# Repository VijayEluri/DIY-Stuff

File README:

Random DIY stuff 
- PCB designs
- CNC projects and motor stepper drivers
- for Arduino Duemilanove
- Python (pygame)

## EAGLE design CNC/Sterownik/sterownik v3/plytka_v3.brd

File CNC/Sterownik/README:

Copyrights - Soki from Elektroda forum - www.elektroda.pl/rtvforum/profile.php?mode=viewprofile&u=8826

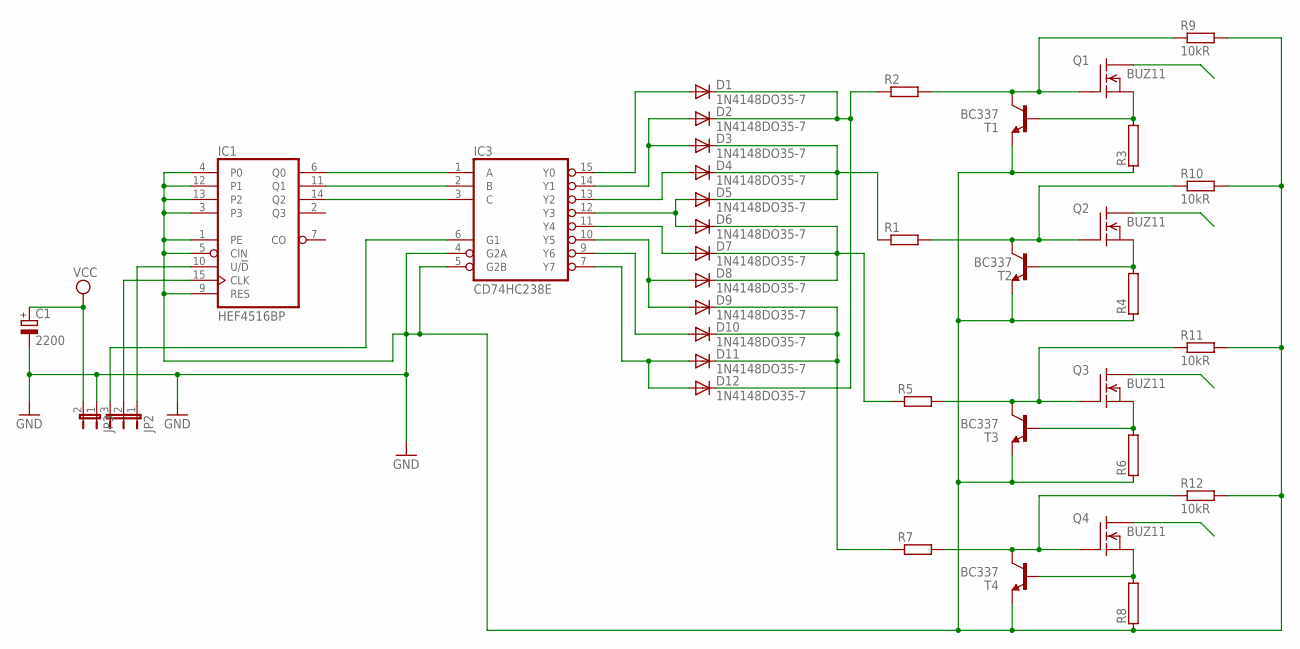
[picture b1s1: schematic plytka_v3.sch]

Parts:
C1: 2200; E5-10,5
D1, D2, D3, D4, D5, D6, D7, D8, D9, D10, D11, D12: 1N4148DO35-7; DO35-7
IC1: HEF4516BP; DIL16
IC3: CD74HC238E; DIL16
JP2: JP2E; JP2
JP3: JP1E; JP1
Q1, Q2, Q3, Q4: BUZ11; TO220
R1, R2, R5, R7: R-EU_0207/15; 0207/15
R3, R4, R6, R8: RKH208-8R; KH208R-8
R9, R10, R11, R12: 10kR; 0207/7
T1, T2, T3, T4: BC337; TO92

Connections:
GND: C1.-, IC1.1 (PE), IC1.3, IC1.4 (P0), IC1.5 (CIN), IC1.8 (VSS), IC1.9 (RES), IC1.12 (P1), IC1.13 (P2), IC3.4 (G2A), IC3.5 (G2B), IC3.8 (GND), JP3.1, R3.1, R4.1, R6.1, R8.1, R9.2, R10.2, R11.2, R12.2, T1.1 (E), T2.1 (E), T3.1 (E), T4.1 (E)
unnamed: IC1.14 (Q2), IC3.3 (C)
unnamed: IC1.11 (Q1), IC3.2 (B)
unnamed: IC1.6 (Q0), IC3.1 (A)
unnamed: IC1.15 (CLK), JP2.2
unnamed: IC1.10 (U/!D), JP2.1
unnamed: IC3.6 (G1), JP2.3
unnamed: D1.A, IC3.15 (Y0)
unnamed: D2.A, D3.A, IC3.14 (Y1)
unnamed: D4.A, IC3.13 (Y2)
unnamed: D5.A, D6.A, IC3.12 (Y3)
unnamed: D7.A, IC3.11 (Y4)
unnamed: D8.A, D9.A, IC3.10 (Y5)
unnamed: D10.A, IC3.9 (Y6)
unnamed: D11.A, D12.A, IC3.7 (Y7)
unnamed: D3.C, D4.C, D5.C, R1.1
unnamed: D9.C, D10.C, D11.C, R7.1
unnamed: Q1.1 (G), R2.2, R9.1, T1.3 (C)
unnamed: Q2.1 (G), R1.2, R10.1, T2.3 (C)
unnamed: Q1.3 (S), R3.2, T1.2 (B)
unnamed: Q2.3 (S), R4.2, T2.2 (B)
unnamed: D6.C, D7.C, D8.C, R5.1
unnamed: Q4.1 (G), R7.2, R12.1, T4.3 (C)
unnamed: Q3.1 (G), R5.2, R11.1, T3.3 (C)
unnamed: Q4.3 (S), R8.2, T4.2 (B)
unnamed: D1.C, D2.C, D12.C, R2.1
unnamed: Q3.3 (S), R6.2, T3.2 (B)
VCC: C1.+, IC1.16 (VDD), IC3.16 (VCC), JP3.2

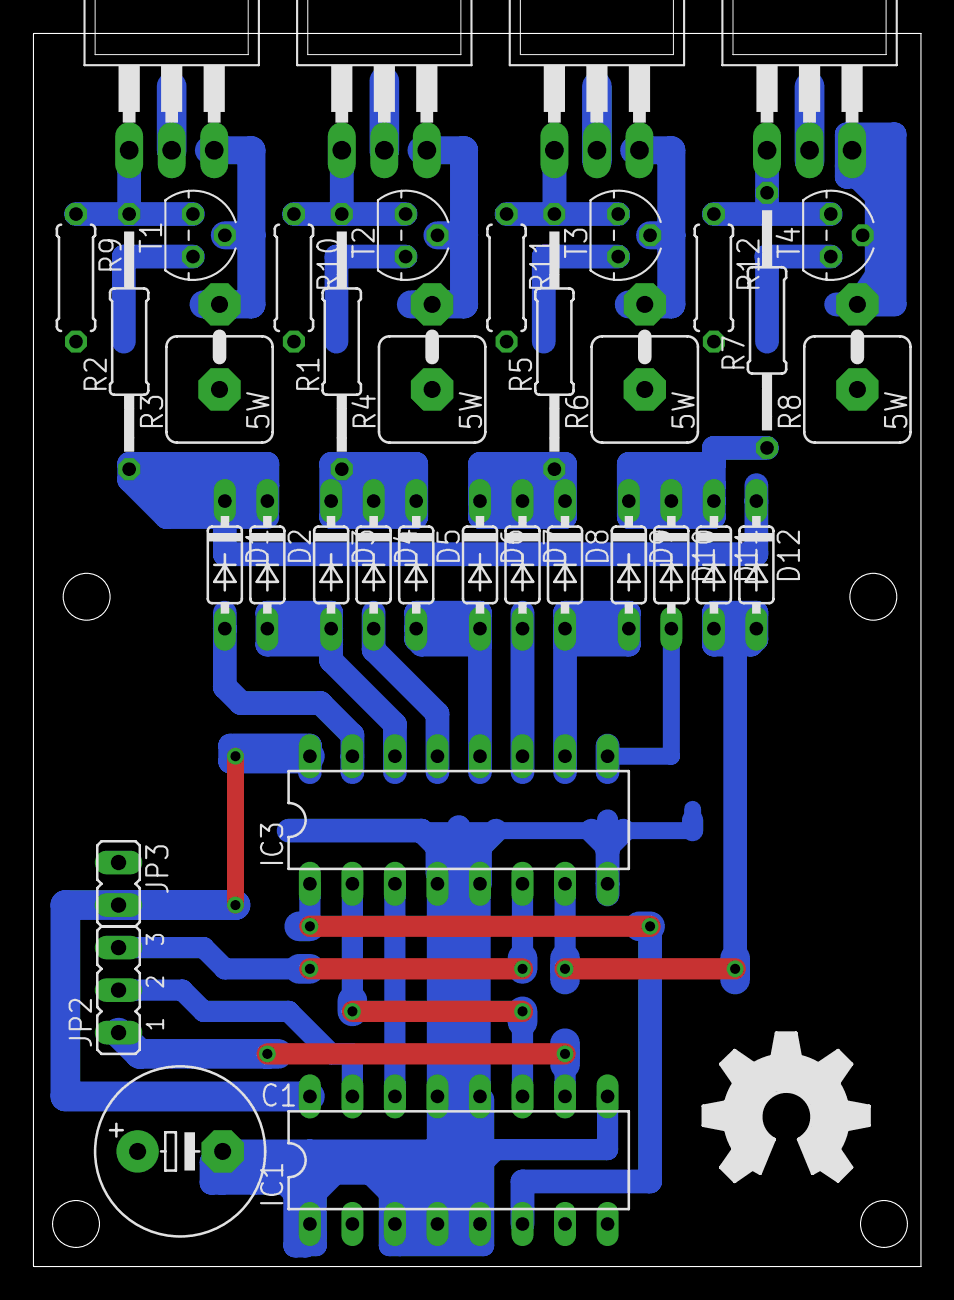
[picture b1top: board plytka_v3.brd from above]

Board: 2 copper layers, 53.0 x 73.7 mm, 38 parts (0 on the bottom side), 28 nets.

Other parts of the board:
U$2: OSHW_FILLX350_NOTEXT

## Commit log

2010-01-03 Added code for Arduino and Python
2010-01-03 Added modules for N800
2010-10-09 Added LCD code
2010-10-09 Added README
2010-10-09 Fixed stupid bugs
2010-10-09 Added simple counter script
2010-10-09 Added comment
2010-10-09 Down counter
2012-02-17 Added driver for Panasonic Lumix
2012-04-13 New DIY stuff
2012-10-01 Metric BBox design - draft
2012-11-18 Dodane PNG z schematem i widokiem plytki
